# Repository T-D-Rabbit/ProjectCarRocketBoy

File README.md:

# RocketBoy – simulator, 9 × TB6612FNG parallel driver board, 3D model

A circular (Ø300 mm) differential-drive robot: two SG-3851218000-60K 12 V gear-motors on L-clamps, two ball casters,
a 3S Molicel pack underneath, and a PCB on top with **9 TB6612FNG modules in parallel** (3 × 3 grid, three enable switches),
an ESP32 DevKit socket and header pins for **every unused ESP32 pin plus a 10-pin expansion header** so a top PCB can be plugged on.

## Quick start – the simulator (this is the thing to submit)

**Double-click `RocketBoy_Simulator.html`** (Chrome, Edge or Firefox; one file, no install, no internet, no server).

| control | action |
|---|---|
| `W` `A` `S` `D` or arrow keys (or the on-screen ▲◀▼▶, hold) | drive / steer (A = left) |
| `Space` | cut power (coast to a stop) |
| **Run hard-coded route** | the robot drives a square with 90° spins by itself (any drive key takes over) |
| `R` / `P` | reset / pause |
| `1` `2` `3` (or the SW1–SW3 boxes) | switch the three STBY enable switches = 3, 6 or 9 driver modules per motor |
| max duty, soft start, sim speed | sliders / tick boxes (turn soft start off to see the 7 A inrush) |
| jam the wheels | stall test: with only SW1 on the module tiles turn red (> 1.2 A rating) |
| mouse drag / wheel, `C` | orbit / zoom the camera, chase-cam on/off |

The window shows the 3D robot, speed / yaw rate, motor currents, battery voltage and charge, the 3×3 module grid (current of each TB6612 module against its 1.2 A rating)
and rolling current / voltage charts.

Verification that was run: the JavaScript model gives **bit-identical** results to the Python model (`python3 simulation/test_js_parity.py`),
and a headless UI test drives it with synthetic key presses (`node simulation/test_simulator_ui.js`). I could not open it in a real browser here,
so if something looks off on your machine tell me the browser and what you see.

Optional (needs Python 3, nothing to install): `python3 simulation/run_all.py` re-runs the batch scenarios (launch, stall, hill, spin, route, PCB copper check)
and writes plots/CSV/`summary.md` to `simulation/results/`; `python3 simulation/build_web_sim.py` rebuilds the HTML.

## 1. How much current?

| situation (simulated) | current per motor | modules needed |
|---|---|---|
| steady driving, flat, 1.73 m/s | **0.5 A** (motor no-load current) | 1 |
| hard-coded route (square with spins) | mean 0.8 A while moving, peak 2.5 A | 1 group (3 modules = 3.6 A rated) |
| 25° ramp at duty 0.7 | 1.2 A | 1 |
| tyres at the traction limit (wheel spin, ≈ 34° slope; also what happens when pushing a wall) | ≈ 1.4 A | 1 |
| **full-duty step from standstill (inrush)** | **6.8 A for ~50 ms** | soft-start the PWM (route uses 3 duty/s) |
| **wheels jammed / gearbox locked** | **6.1 – 6.5 A per motor (7.5 A on the bare 12 V terminals), ≈ 13 A from the battery for both** | ≥ 2 groups (or stall-detect in firmware) |

One group (3 modules per motor channel: 3.6 A continuous, 9.6 A pulse) covers all normal driving; groups 2 and 3 (6/9 modules, 7.2/10.8 A) are insurance for jams and heavier motors.

> **Stall current = 7.5 A (your figure)**; the stall rows in `Johnson Motor.pdf` are blank. The model uses R = 12 V / 7.5 A = 1.6 Ω and takes Ke from the 300 rpm no-load point
> (stall torque ≈ 25 kgf·cm, derived). Cross-check: it gives 229 rpm at 6 kgf·cm against 220 ± 22 rpm in the PDF, so the two agree. In the robot the pack, driver and wiring resistance
> bring the stalled current down to 6.1 – 6.5 A. Change `I_STALL` in `simulation/params.py` to try other values.

## 2. Mistakes found in the original design and what was changed

| # | original | problem | fix |
|---|---|---|---|
| 1 | ESP32 `5Vin` on net `VCC` = battery (9 – 12.6 V) | over-voltages the DevKit regulator / USB rail | new `+5V` net from an external buck module (`J1` in, `J2` out); battery net renamed `VBAT` |
| 2 | `STBY` of all modules tied to `VCCQ` | no enable switches – modules always on | `STBY1…3` per group (= per PCB column: U1-3, U4-6, U7-9), SPDT slide switches `SW1…3` (ON → 3V3, OFF → GND) |
| 3 | ESP32 pad 21 tied to GND | on the 38-pin DevKit that pin is `CMD` (flash line) | left open (no-connect) |
| 4 | no outline / holes, a few 0.2 mm tracks | board unfinished | 155 × 208 mm outline, 4 × Ø3.2 mm holes on the STEP pattern (±75, ±100 mm), fully routed, B.Cu GND pour |
| 5 | 1.9 mm pads for battery/motors | cannot carry 6 A | 5.08 mm screw terminals, 3 – 5 mm trunks, 2 oz copper recommended |
| 6 | no bulk capacitance | motor-supply spikes | `C1–C3` 470 µF / 25 V on VBAT |
| 7 | no way to attach a controller / top board | – | headers `J3`, `J4`, `J5` (below) |
| 8 | *(my own earlier error)* clamps shown under the chassis | the 26.7 mm axis height is from the flange face, so under the plate the chassis would be 76 mm off the floor | clamps are on the **top** face; wheel Ø110 → chassis top 28.3 mm, underside 25.3 mm above the floor |

Not verifiable here, please check against your parts: the TB6612 breakout pin order (`pad 6 = BO1, pad 7 = BO2` was kept; if your module prints BO2 first the right motor
just runs reversed – swap the wires), and the ESP32 DevKit pinout. GPIO12 (AIN1) is the flash-voltage strapping pin; do not add a pull-up.

### Header pins for a top PCB (all 2.54 mm, shown as tall male pins in the 3D model; the PCB has the plated holes, fit sockets or pins as you prefer)

* **`J5`** – west ESP32 row, 1×8: `1 3V3 · 2 EN · 3 GPIO36 · 4 GPIO39 · 5 GPIO34 · 6 GPIO35 · 7 GPIO32 · 8 GPIO33` (GPIO34-39 are input-only, usable as ADC1).
* **`J4`** – east ESP32 row, 1×16: `1 GND · 2 GPIO23 · 3 GPIO22 · 4 GPIO1/TX0 · 5 GPIO3/RX0 · 6 GPIO21 · 7 GND · 8 GPIO19 · 9 GPIO18 · 10 GPIO5 · 11 GPIO17 · 12 GPIO16 · 13 GPIO4 · 14 GPIO0 · 15 GPIO2 · 16 GPIO15`.
  GPIO0/2/5/12/15 are boot-strapping pins – keep them high-impedance at reset.
* **`J3`** – expansion, 1×10: `1 5V · 2 3V3 · 3 GND · 4 BIN1 · 5 BIN2 · 6 PWMB · 7 AIN2 · 8 AIN1 · 9 GND · 10 PWMA` – the motor-control nets (same as ESP32 GPIO25/26/27/14/12/13).
  To drive the motors from another board, **remove the ESP32** so two outputs never fight. STBY stays on the three slide switches.
* Not broken out: GPIO6-11 (connected to the DevKit's flash – unusable) and the pins already used by the driver bank (GPIO12/13/14/25/26/27).
* The top board can sit on the same four M3 holes (150 × 200 mm pattern) with longer standoffs.

## 3. PCB (`RocketBoy/RocketBoy.kicad_pcb`)

* 2 layers, A3 sheet, **155 × 208 mm** (155 keeps clear of the motors' rear bosses), board centre = chassis centre, **front = top edge** (switches at the front edge, USB of the ESP32 at the rear edge).
* **Architecture** – one column of three modules = one enable group: each module pin goes by a short `F.Cu` stub to a via; vertical `B.Cu` "bus lanes" run along the column
  (VBAT 3 mm, GND 3 mm, motor outputs 2 mm, logic 0.3 mm); the lanes of the three columns are joined by horizontal `F.Cu` trunks (VBAT 5 mm, motor outputs 3.5 mm) that end at the battery / left / right motor
  screw terminals (`BT1`, `U11`, `U12`); the six control lines continue to the ESP32 control pins and `J3`.
* Parts added: `SW1–3`, `C1–3`, `J1/J2` (5 V buck in/out), `J3/J4/J5` (headers above), `H1–H4` (M3). Their footprints/symbols are in `RocketBoy/RocketBoy.pretty` and `RocketBoy.kicad_sym`
  (registered via `fp-lib-table` / `sym-lib-table`); your original `Control_Modules:` and `MCU:` footprints are untouched. Recommended in the battery lead: 10 A fuse and a main switch.

Checks run (KiCad is not available in the build environment – **please run KiCad's ERC/DRC once and press B to fill zones**):

| check | result |
|---|---|
| independent clearance check, all copper, 0.20 mm rule | 0 violations |
| every non-GND net electrically connected | all connected |
| flood-fill of the B.Cu pour (0.4 mm clearance) | every GND pad / via / lane reaches the main pour |
| edge ≥ 0.5 mm, drill-to-drill / drill-to-copper ≥ 0.25 mm | 0 violations |
| schematic netlist vs PCB netlist (`tools/compare_netlists.py`) | identical (38 nets) |

## 4. Mechanics and 3D model (`model3d/out/`)

* Inputs: `Chassis file.step` (Ø300 × 3 mm disc, PCB holes ±75 / ±100, 12 clamp holes, caster slots), `L Clamp.pdf` (1.5 mm steel, flange 22 mm, Ø22 bore + 12 holes, axis 26.7 mm above the flange),
  `Johnson Motor.pdf` (gearbox Ø37 × 25, can Ø29 × 37.8, Ø6 × 30 shaft).
* Clamps on the **top** face, motors inwards, wheels outside. **Wheel Ø110 × 25 mm (assumed)** → chassis underside 25.3 mm above the floor (room for the 3 × 18650 pack, buck module, voltage indicator; casters 25.3 mm tall).
  PCB on four **M3 × 40 mm** standoffs so it passes above the motor rear bosses.
* Files: `rocketboy_assembly.stl` (+ body / wheel STLs), `rocketboy.obj/.mtl`, `rocketboy_route.gif` (the route animation), `preview_*.png`. Units mm, x = wheel axis, y = forward, z = up.
  A visual / fit model rebuilt from the STEP's dimensions, not a converted STEP. Rebuild: `python3 model3d/make_outputs.py`.

## 5. Simulation model and results

3S Li-ion (OCV curve + 101 mΩ) → TB6612 bank (random ±25 % R_on spread decides how current shares between modules) → DC motors fitted to the datasheet rated point →
tanh tyre-force model → differential-drive body. Hard-coded route: 4 × [drive 2 s at duty 0.6, pause, spin left 0.368 s (calibrated to 90°), settle], duty slew-limited to 3/s.
Results (see `simulation/results/summary.md`): top speed 1.73 m/s, 0 → 1 m/s in 0.18 s, spin 272 °/s; route 15.2 s / 7.9 m, ends 91 mm and +3.7° from the start (open loop drifts),
peak 2.6 A, 6.9 mAh, battery ≥ 11.73 V, worst module 1.11 A. A PCB copper check (S6) compares the trace widths in the PCB file with the currents (2 oz copper needed for a jam; with both motors jammed the 5 mm VBAT trunk carries 13.4 A, slightly above its 12.7 A rating, so use a **10 A fuse**).

Assumptions (all in `simulation/params.py`): mass 2.2 kg, 1:60 gearbox and rotor inertia, wheel, tyre μ 0.8, battery 2.8 Ah / 22 mΩ per cell, R_on 0.5 Ω ± 25 %.
Not modelled: lateral tyre slip, motor inductance (PWM-averaged), thermal behaviour, collisions.

## 6. Firmware (`firmware/rocketboy_hardcoded/`)

ESP32 sketch that runs the same route (20 kHz LEDC PWM, schematic pins, 5 ms loop, same slew limit); `route.h` is generated from the simulation. **Not tested on hardware** – lift the wheels first.

## 7. Reproducing

```
python3 docs/make_specs_pdf.py          # docs/SPECS.md -> docs/RocketBoy_Specs.pdf (pure Python)
python3 simulation/run_all.py          # batch scenarios + route.h + route_30hz.json
python3 simulation/build_web_sim.py    # RocketBoy_Simulator.html
python3 simulation/test_js_parity.py   # JS model == Python model
node simulation/test_simulator_ui.js   # headless UI test
python3 model3d/make_outputs.py        # STL / OBJ / GIF / renders
python3 tools/build_pcb.py && python3 tools/build_sch.py && python3 tools/compare_netlists.py   # KiCad files (start from tools/originals/)
```
Re-running the KiCad generators overwrites hand edits made in KiCad afterwards – treat them as the one-time "design completion" step.

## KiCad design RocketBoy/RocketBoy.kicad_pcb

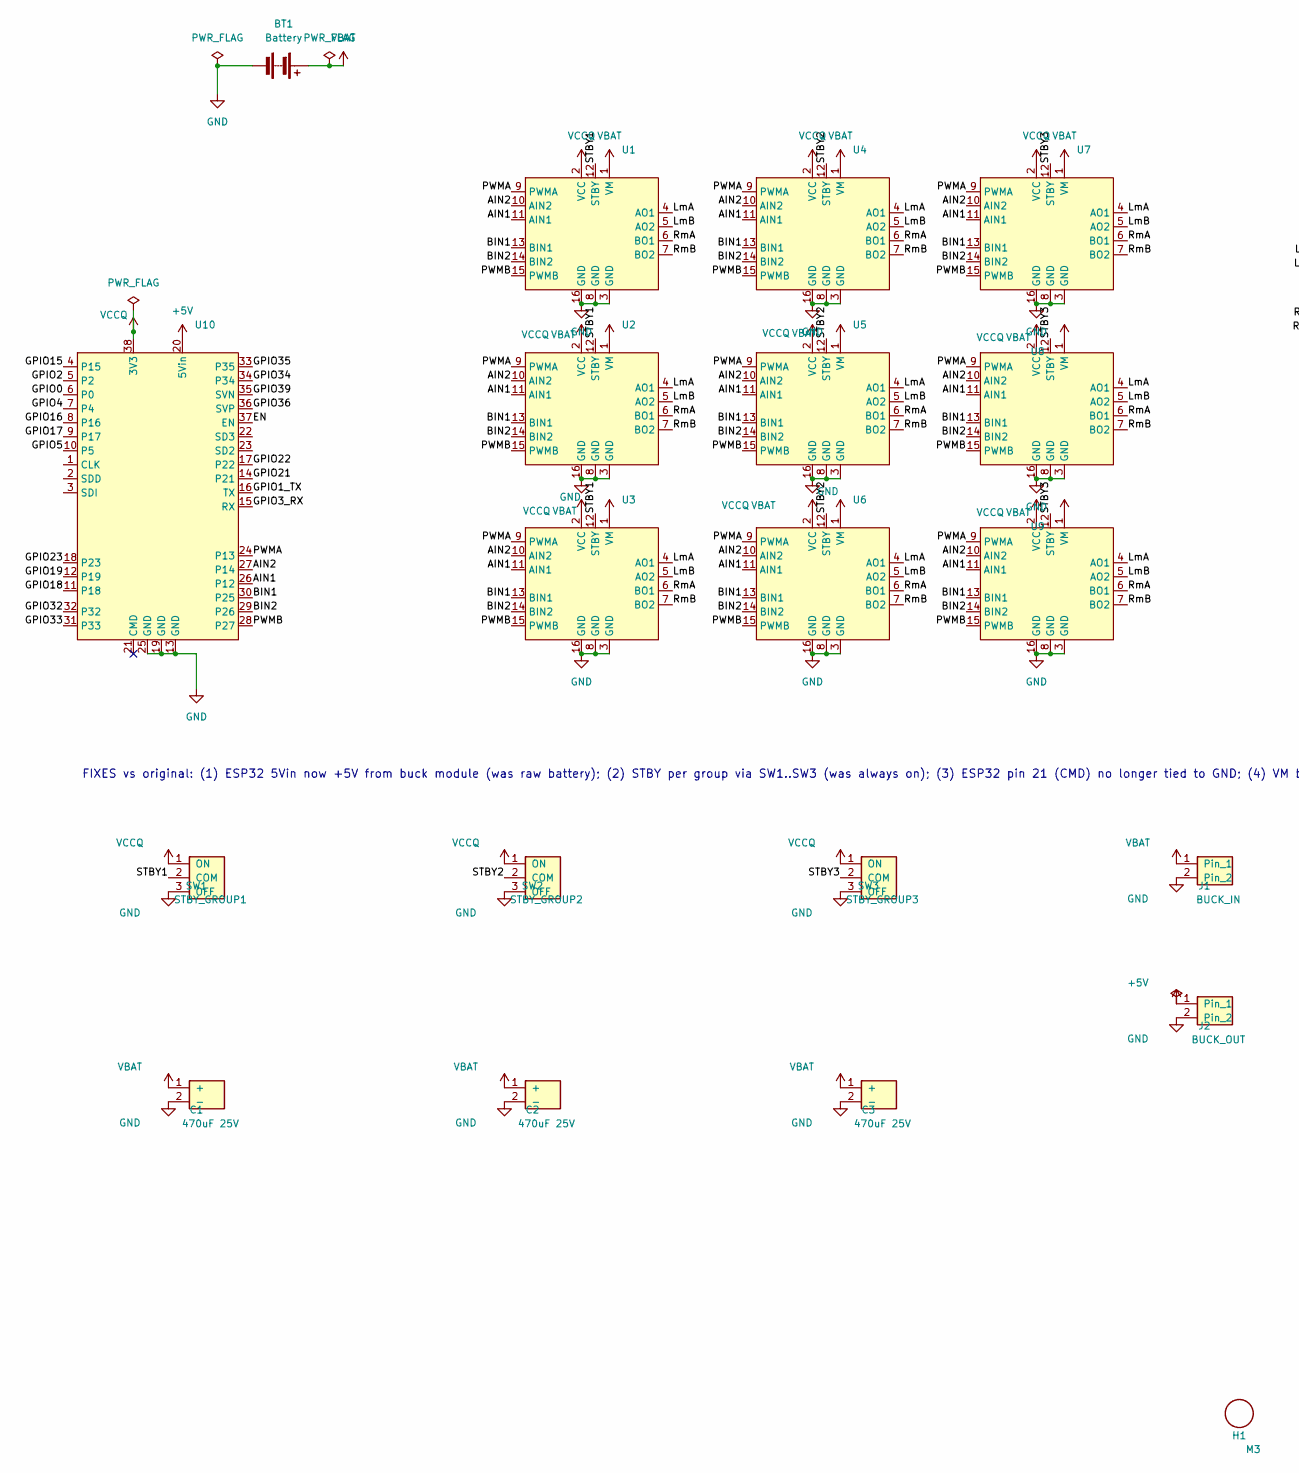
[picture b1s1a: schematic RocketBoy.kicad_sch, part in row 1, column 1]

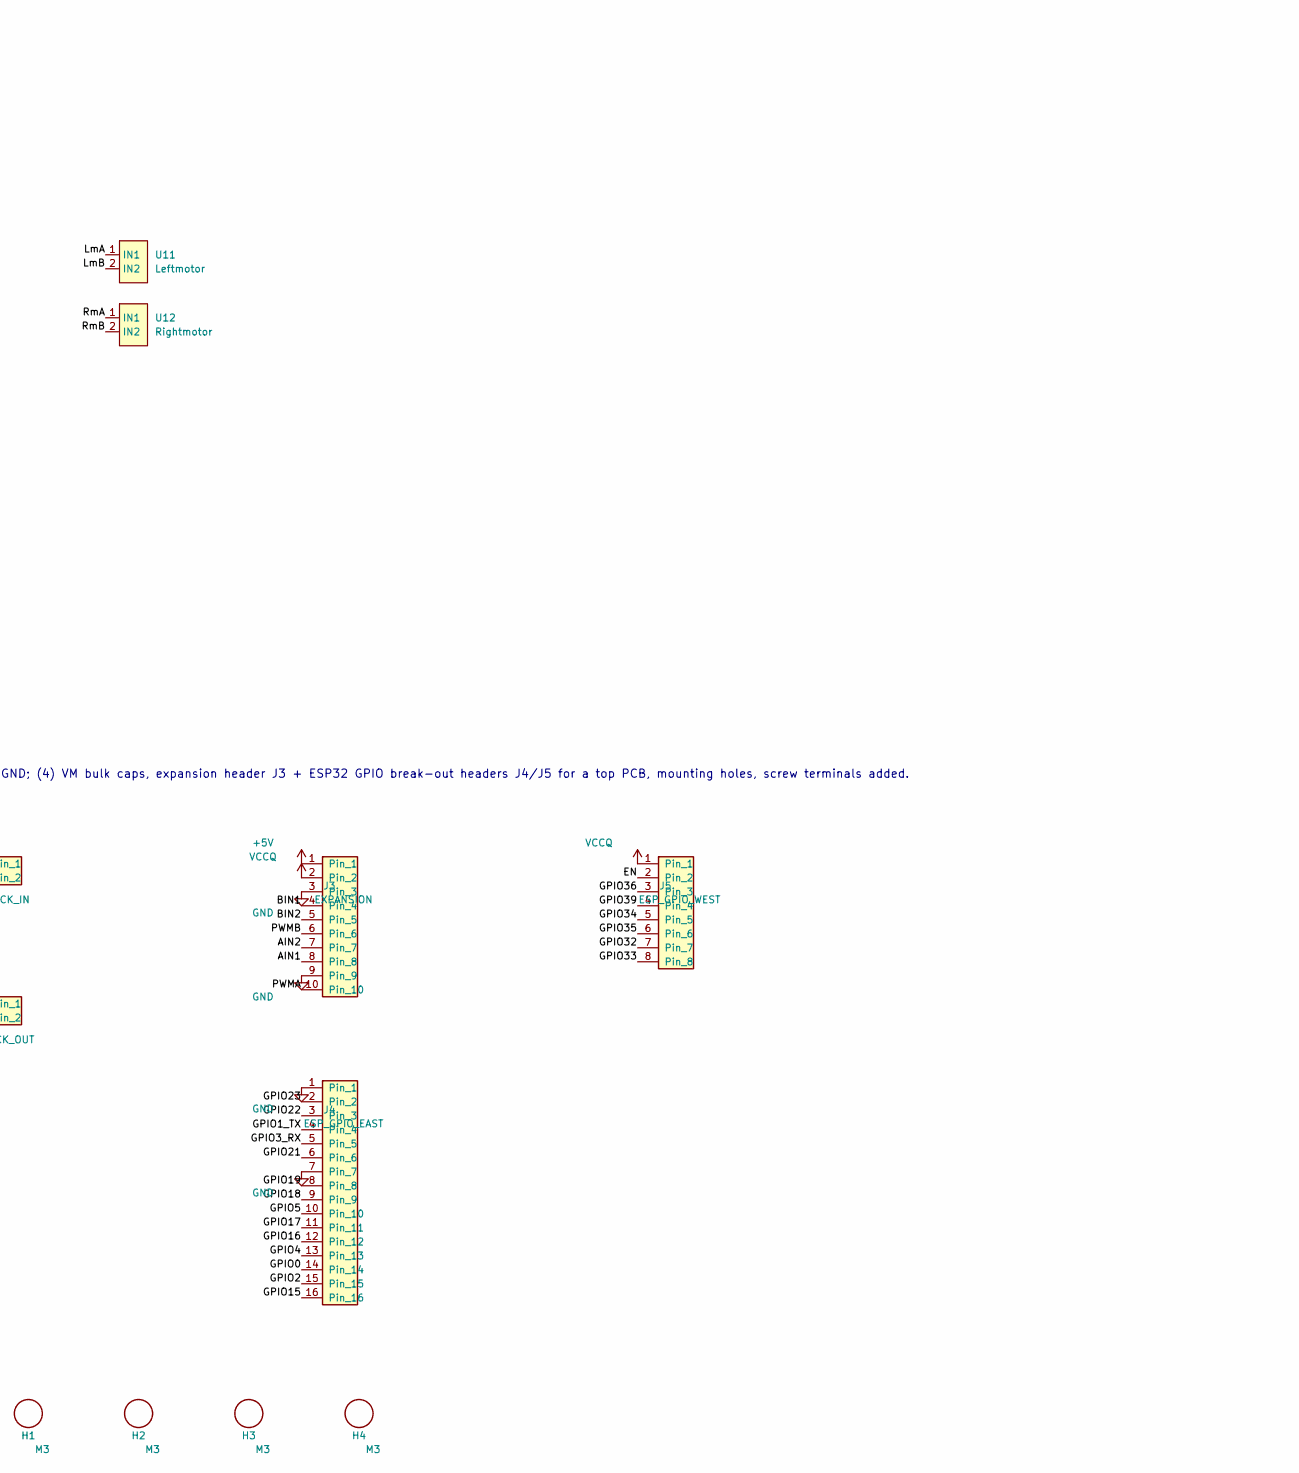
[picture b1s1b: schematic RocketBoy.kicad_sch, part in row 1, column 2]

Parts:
BT1: Battery; TerminalBlock_5.08mm_2P_Vertical
C1, C2, C3: 470uF 25V; CP_Radial_D10.0mm_P5.00mm
H1, H2, H3, H4: M3; MountingHole_3.2mm_M3
J1: BUCK_IN; PinHeader_1x02_P2.54mm_Vertical
J2: BUCK_OUT; PinHeader_1x02_P2.54mm_Vertical
J3: EXPANSION; PinHeader_1x10_P2.54mm_Vertical
J4: ESP_GPIO_EAST; PinHeader_1x16_P2.54mm_Vertical
J5: ESP_GPIO_WEST; PinHeader_1x08_P2.54mm_Vertical
SW1: STBY_GROUP1; SPDT_Slide_1x03_P2.54mm
SW2: STBY_GROUP2; SPDT_Slide_1x03_P2.54mm
SW3: STBY_GROUP3; SPDT_Slide_1x03_P2.54mm
U1, U2, U3, U4, U5, U6, U7, U8, U9: TB6612FND_Motor_Driver
U10: ESP32Wroom
U11: Leftmotor; TerminalBlock_5.08mm_2P_Vertical
U12: Rightmotor; TerminalBlock_5.08mm_2P_Vertical

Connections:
+5V: J2.1, J3.1 (5V), U10.20 (5Vin)
/AIN1: J3.8 (AIN1), U1.11 (AIN1), U2.11 (AIN1), U3.11 (AIN1), U4.11 (AIN1), U5.11 (AIN1), U6.11 (AIN1), U7.11 (AIN1), U8.11 (AIN1), U9.11 (AIN1), U10.26 (P12)
/AIN2: J3.7 (AIN2), U1.10 (AIN2), U2.10 (AIN2), U3.10 (AIN2), U4.10 (AIN2), U5.10 (AIN2), U6.10 (AIN2), U7.10 (AIN2), U8.10 (AIN2), U9.10 (AIN2), U10.27 (P14)
/BIN1: J3.4 (BIN1), U1.13 (BIN1), U2.13 (BIN1), U3.13 (BIN1), U4.13 (BIN1), U5.13 (BIN1), U6.13 (BIN1), U7.13 (BIN1), U8.13 (BIN1), U9.13 (BIN1), U10.30 (P25)
/BIN2: J3.5 (BIN2), U1.14 (BIN2), U2.14 (BIN2), U3.14 (BIN2), U4.14 (BIN2), U5.14 (BIN2), U6.14 (BIN2), U7.14 (BIN2), U8.14 (BIN2), U9.14 (BIN2), U10.29 (P26)
/EN: J5.2 (EN), U10.37 (EN)
/GPIO0: J4.14 (GPIO0), U10.6 (P0)
/GPIO1_TX: J4.4 (TX0_GPIO1), U10.16 (TX)
/GPIO2: J4.15 (GPIO2), U10.5 (P2)
/GPIO3_RX: J4.5 (RX0_GPIO3), U10.15 (RX)
/GPIO4: J4.13 (GPIO4), U10.7 (P4)
/GPIO5: J4.10 (GPIO5), U10.10 (P5)
/GPIO15: J4.16 (GPIO15), U10.4 (P15)
/GPIO16: J4.12 (GPIO16), U10.8 (P16)
/GPIO17: J4.11 (GPIO17), U10.9 (P17)
/GPIO18: J4.9 (GPIO18), U10.11 (P18)
/GPIO19: J4.8 (GPIO19), U10.12 (P19)
/GPIO21: J4.6 (GPIO21), U10.14 (P21)
/GPIO22: J4.3 (GPIO22), U10.17 (P22)
/GPIO23: J4.2 (GPIO23), U10.18 (P23)
/GPIO32: J5.7 (GPIO32), U10.32
/GPIO33: J5.8 (GPIO33), U10.31 (P33)
/GPIO34: J5.5 (GPIO34), U10.34
/GPIO35: J5.6 (GPIO35), U10.33 (P35)
/GPIO36: J5.3 (GPIO36_SVP), U10.36 (SVP)
/GPIO39: J5.4 (GPIO39_SVN), U10.35 (SVN)
/LmA: U1.4 (AO1), U2.4 (AO1), U3.4 (AO1), U4.4 (AO1), U5.4 (AO1), U6.4 (AO1), U7.4 (AO1), U8.4 (AO1), U9.4 (AO1), U11.1 (IN1)
/LmB: U1.5 (AO2), U2.5 (AO2), U3.5 (AO2), U4.5 (AO2), U5.5 (AO2), U6.5 (AO2), U7.5 (AO2), U8.5 (AO2), U9.5 (AO2), U11.2 (IN2)
/PWMA: J3.10 (PWMA), U1.9 (PWMA), U2.9 (PWMA), U3.9 (PWMA), U4.9 (PWMA), U5.9 (PWMA), U6.9 (PWMA), U7.9 (PWMA), U8.9 (PWMA), U9.9 (PWMA), U10.24 (P13)
/PWMB: J3.6 (PWMB), U1.15 (PWMB), U2.15 (PWMB), U3.15 (PWMB), U4.15 (PWMB), U5.15 (PWMB), U6.15 (PWMB), U7.15 (PWMB), U8.15 (PWMB), U9.15 (PWMB), U10.28 (P27)
/RmA: U1.6 (BO1), U2.6 (BO1), U3.6 (BO1), U4.6 (BO1), U5.6 (BO1), U6.6 (BO1), U7.6 (BO1), U8.6 (BO1), U9.6 (BO1), U12.1 (IN1)
/RmB: U1.7 (BO2), U2.7 (BO2), U3.7 (BO2), U4.7 (BO2), U5.7 (BO2), U6.7 (BO2), U7.7 (BO2), U8.7 (BO2), U9.7 (BO2), U12.2 (IN2)
/STBY1: SW1.2 (COM), U1.12 (STBY), U2.12 (STBY), U3.12 (STBY)
/STBY2: SW2.2 (COM), U4.12 (STBY), U5.12 (STBY), U6.12 (STBY)
/STBY3: SW3.2 (COM), U7.12 (STBY), U8.12 (STBY), U9.12 (STBY)
GND: BT1.2 (-), C1.2 (-), C2.2 (-), C3.2 (-), J1.2, J2.2, J3.3 (GND), J3.9 (GND), J4.1 (GND), J4.7 (GND), SW1.3 (OFF), SW2.3 (OFF), SW3.3 (OFF), U1.3 (GND), U1.8 (GND), U1.16 (GND), U2.3 (GND), U2.8 (GND), U2.16 (GND), U3.3 (GND), U3.8 (GND), U3.16 (GND), U4.3 (GND), U4.8 (GND), U4.16 (GND), U5.3 (GND), U5.8 (GND), U5.16 (GND), U6.3 (GND), U6.8 (GND), U6.16 (GND), U7.3 (GND), U7.8 (GND), U7.16 (GND), U8.3 (GND), U8.8 (GND), U8.16 (GND), U9.3 (GND), U9.8 (GND), U9.16 (GND), U10.13 (GND), U10.19 (GND), U10.25 (GND)
VBAT: BT1.1 (+), C1.1 (+), C2.1 (+), C3.1 (+), J1.1, U1.1 (VM), U2.1 (VM), U3.1 (VM), U4.1 (VM), U5.1 (VM), U6.1 (VM), U7.1 (VM), U8.1 (VM), U9.1 (VM)
VCCQ: J3.2 (3V3), J5.1 (3V3), SW1.1 (ON), SW2.1 (ON), SW3.1 (ON), U1.2 (VCC), U2.2 (VCC), U3.2 (VCC), U4.2 (VCC), U5.2 (VCC), U6.2 (VCC), U7.2 (VCC), U8.2 (VCC), U9.2 (VCC), U10.38 (3V3)

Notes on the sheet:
FIXES vs original: (1) ESP32 5Vin now +5V from buck module (was raw battery); (2) STBY per group via SW1..SW3 (was always on); (3) ESP32 pin 21 (CMD) no longer tied to GND; (4) VM bulk caps, expansion header J3 + ESP32 GPIO break-out headers J4/J5 for a top PCB, mounting holes, screw terminals adde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

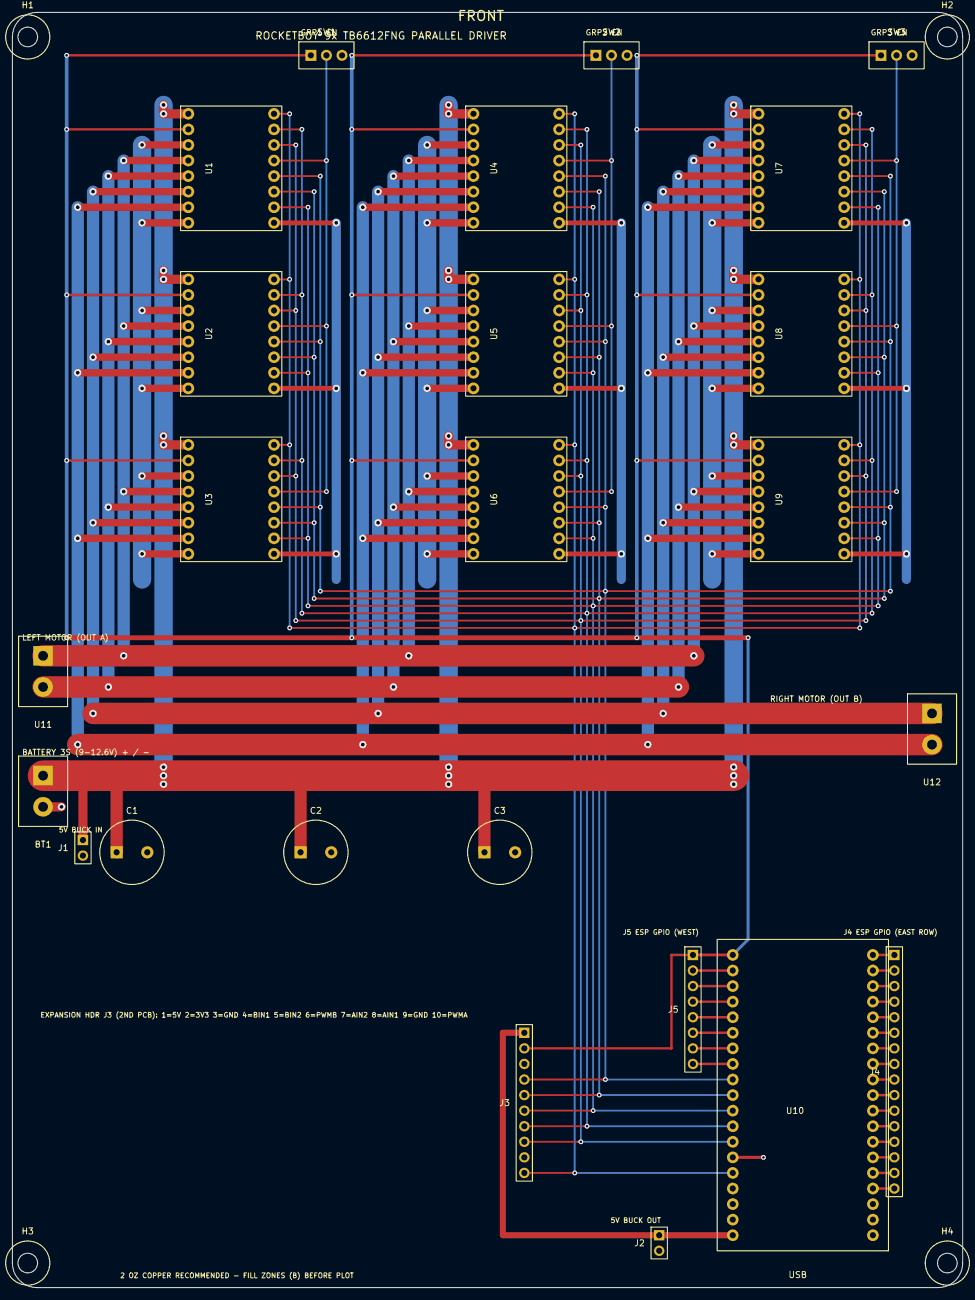
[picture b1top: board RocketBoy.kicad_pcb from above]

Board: 2 copper layers, 155.0 x 208.0 mm, 28 parts (0 on the bottom side), 38 nets.

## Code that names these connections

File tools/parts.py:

"""Single source of truth for the NEW parts that are added to the RocketBoy design.

Both build_pcb.py (footprints, placement, routing) and build_sch.py (symbols, labels) import
this file, so the schematic and the PCB can never disagree about reference designators,
pin numbers or net names.
"""
import uuid as _uuid


def _u(name):
    return str(_uuid.uuid5(_uuid.UUID("6f0c9d3e-2b7a-4c11-9a55-0d2c3e4f5a60"), name))


# ---------------------------------------------------------------- footprint families
FP_TERM = "RocketBoy:TerminalBlock_5.08mm_2P_Vertical"
FP_SW = "RocketBoy:SPDT_Slide_1x03_P2.54mm"
FP_CAP = "RocketBoy:CP_Radial_D10.0mm_P5.00mm"
FP_HDR2 = "RocketBoy:PinHeader_1x02_P2.54mm_Vertical"
FP_HDR10 = "RocketBoy:PinHeader_1x10_P2.54mm_Vertical"
FP_HDR16 = "RocketBoy:PinHeader_1x16_P2.54mm_Vertical"
FP_HDR8 = "RocketBoy:PinHeader_1x08_P2.54mm_Vertical"
FP_HOLE = "RocketBoy:MountingHole_3.2mm_M3"

# ---------------------------------------------------------------- new parts
# ref: dict(value, fp, sym, pins=[(num, name, net)], uuid)
PARTS = {}


def add(ref, value, fp, sym, pins, desc=""):
    PARTS[ref] = dict(ref=ref, value=value, fp=fp, sym=sym, pins=pins, uuid=_u(ref), desc=desc)


for g in (1, 2, 3):
    add("SW%d" % g, "STBY_GROUP%d" % g, FP_SW, "RocketBoy:SW_SPDT_Slide",
        [("1", "ON", "VCCQ"), ("2", "COM", "/STBY%d" % g), ("3", "OFF", "GND")],
        "Group %d enable: ON = STBY high (3 TB6612 modules active), OFF = STBY low (outputs Hi-Z)" % g)

for i in (1, 2, 3):
    add("C%d" % i, "470uF 25V", FP_CAP, "RocketBoy:CP_Polarized",
        [("1", "+", "VBAT"), ("2", "-", "GND")], "VM bulk capacitor %d" % i)

add("J1", "BUCK_IN", FP_HDR2, "RocketBoy:Conn_01x02",
    [("1", "Pin_1", "VBAT"), ("2", "Pin_2", "GND")], "Input to external 5 V buck module (VBAT, GND)")
add("J2", "BUCK_OUT", FP_HDR2, "RocketBoy:Conn_01x02",
    [("1", "Pin_1", "+5V"), ("2", "Pin_2", "GND")], "Output of external 5 V buck module (+5V, GND)")
add("J3", "EXPANSION", FP_HDR10, "RocketBoy:Conn_01x10",
    [("1", "5V", "+5V"), ("2", "3V3", "VCCQ"), ("3", "GND", "GND"), ("4", "BIN1", "/BIN1"), ("5", "BIN2", "/BIN2"),
     ("6", "PWMB", "/PWMB"), ("7", "AIN2", "/AIN2"), ("8", "AIN1", "/AIN1"), ("9", "GND", "GND"), ("10", "PWMA", "/PWMA")],
    "Expansion header for a second PCB / controller: 1=5V 2=3V3 3=GND 4=BIN1 5=BIN2 6=PWMB 7=AIN2 8=AIN1 9=GND 10=PWMA "
    "(same nets as the ESP32 control pins, remove the ESP32 when the other board drives them)")
# ---- break-out of every usable, still-unused ESP32 pin for a top PCB
# east column of the ESP32 socket (DevKit pads 19..4, listed top -> bottom on the board)
ESP_EAST = [("19", "GND", "GND"), ("18", "GPIO23", "/GPIO23"), ("17", "GPIO22", "/GPIO22"), ("16", "TX0_GPIO1", "/GPIO1_TX"),
            ("15", "RX0_GPIO3", "/GPIO3_RX"), ("14", "GPIO21", "/GPIO21"), ("13", "GND", "GND"), ("12", "GPIO19", "/GPIO19"),
            ("11", "GPIO18", "/GPIO18"), ("10", "GPIO5", "/GPIO5"), ("9", "GPIO17", "/GPIO17"), ("8", "GPIO16", "/GPIO16"),
            ("7", "GPIO4", "/GPIO4"), ("6", "GPIO0", "/GPIO0"), ("5", "GPIO2", "/GPIO2"), ("4", "GPIO15", "/GPIO15")]
# west column (DevKit pads 38..31)
ESP_WEST = [("38", "3V3", "VCCQ"), ("37", "EN", "/EN"), ("36", "GPIO36_SVP", "/GPIO36"), ("35", "GPIO39_SVN", "/GPIO39"),
            ("34", "GPIO34", "/GPIO34"), ("33", "GPIO35", "/GPIO35"), ("32", "GPIO32", "/GPIO32"), ("31", "GPIO33", "/GPIO33")]
add("J4", "ESP_GPIO_EAST", FP_HDR16, "RocketBoy:Conn_01x16",
    [(str(k + 1), nm, net) for k, (pad, nm, net) in enumerate(ESP_EAST)],
    "Break-out of the east ESP32 pin row (DevKit pads 19..4): GND, GPIO23/22/1/3/21, GND, GPIO19/18/5/17/16/4/0/2/15. "
    "Flash pins GPIO6-11 are NOT broken out.")
add("J5", "ESP_GPIO_WEST", FP_HDR8, "RocketBoy:Conn_01x08",
    [(str(k + 1), nm, net) for k, (pad, nm, net) in enumerate(ESP_WEST)],
    "Break-out of the west ESP32 pin row (DevKit pads 38..31): 3V3, EN, GPIO36/39/34/35 (input only), GPIO32/33")
for i in range(1, 5):
    add("H%d" % i, "M3", FP_HOLE, "RocketBoy:MountingHole", [], "M3 mounting hole (chassis pattern)")

# ESP32 pad -> net map (the original design only wired the 6 motor-control pads, 5V, 3V3, GND)
ESP_NETS = {   # filled below with the break-out pins too
    "20": "+5V",            # was VBAT (12 V) -> FIXED: now 5 V from the buck module
    "38": "VCCQ",           # 3V3
    "21": None,             # was GND but this DevKit pin is CMD (flash) -> now left open
    "24": "/PWMA", "26": "/AIN1", "27": "/AIN2", "28": "/PWMB", "29": "/BIN2", "30": "/BIN1",
}
# hole pattern of the chassis STEP: (+-75, +-100)
HOLES = [(-75.0, -100.0), (75.0, -100.0), (-75.0, 100.0), (75.0, 100.0)]

for _pad, _nm, _net in ESP_EAST + ESP_WEST:
    if _net not in ("GND", "VCCQ"):
        ESP_NETS[_pad] = _net

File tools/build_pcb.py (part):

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        ("5", 12.70, "AO2"), ("6", 15.24, "BO1"), ("7", 17.78, "BO2"), ("8", 20.32, "GND")]
RIGHT = [("9", 2.54, "PWMA"), ("10", 5.08, "AIN2"), ("11", 7.62, "AIN1"), ("12", 10.16, "STBY"),
         ("13", 12.70, "BIN1"), ("14", 15.24, "BIN2"), ("15", 17.78, "PWMB"), ("16", 20.32, "GND")]
PIN_NET = {"VM": "VBAT", "VCC": "VCCQ", "GND": "GND", "AO1": "/LmA", "AO2": "/LmB", "BO1": "/RmA",
           "BO2": "/RmB", "PWMA": "/PWMA", "AIN1": "/AIN1", "AIN2": "/AIN2", "PWMB": "/PWMB",
           "BIN1": "/BIN1", "BIN2": "/BIN2"}
LOGIC_ORDER = ["/PWMA", "/AIN1", "/AIN2", "/PWMB", "/BIN2", "/BIN1"]     # west -> east lane order
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place_part("J2", 28.0, 95.46)       # BUCK_OUT (+5V, GND)
# expansion header for a second PCB: pin rows are aligned with the ESP32 control-pad rows
EXP_X = 6.0
EXP_Y0 = ESP_YE - 35.56            # pin 1 at 62.44; pins 4..10 land on the BIN1..PWMA rows of the ESP32
place_part("J3", EXP_X, EXP_Y0)
# break-out headers for every unused, usable ESP32 pin (rows aligned with the ESP32 pad rows)
ESP_EAST_X = ESP_XP + 22.86 + 3.5
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    emit_custom(ref)

# ------------------------------------------------------------------ user's terminal footprints (BT1/U11/U12)
term_pins = {"BT1": [("1", "VBAT"), ("2", "GND")], "U11": [("1", "/LmA"), ("2", "/LmB")], "U12": [("1", "/RmA"), ("2", "/RmB")]}
for ref, (tx, ty) in TERM.items():
    b = fp_blocks[ref]
    # swap library reference to the new terminal-block footprint and rebuild its pads
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# ------------------------------------------------------------------ expansion header wiring
j3 = {q.num: q for q in board.pads if q.ref.startswith("J3.")}
# control pins: F.Cu from the header pin east to a via on the (B.Cu) logic lane of column 2 at the same y
for pin, net in (("4", "/BIN1"), ("5", "/BIN2"), ("6", "/PWMB"), ("7", "/AIN2"), ("8", "/AIN1"), ("10", "/PWMA")):
    hp = j3[pin]
    lx = east_x(1, net)
    assert abs(hp.y - esp_pad(ESP_CTRL[net]).y) < 1e-6, (pin, hp.y)
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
